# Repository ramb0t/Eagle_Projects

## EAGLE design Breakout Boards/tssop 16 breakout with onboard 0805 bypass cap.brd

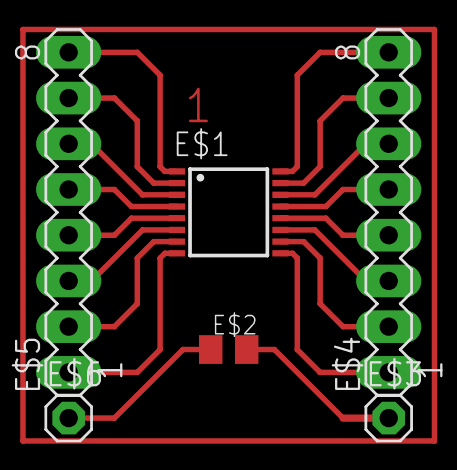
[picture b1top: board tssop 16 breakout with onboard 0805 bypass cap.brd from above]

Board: 2 copper layers, 6 parts (0 on the bottom side), 18 nets.

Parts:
E$1: TSSOP16
E$2: C0805K
E$3, E$6: 1X01
E$4, E$5: MA08-1

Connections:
S$1: E$1.1, E$5.8
S$2: E$1.2, E$5.7
S$3: E$1.3, E$5.6
S$4: E$1.4, E$5.5
S$5: E$1.5, E$5.4
S$6: E$1.6, E$5.3
S$7: E$1.7, E$5.2
S$8: E$1.8, E$5.1
S$9: E$1.9, E$4.1
S$10: E$1.10, E$4.2
S$11: E$1.11, E$4.3
S$12: E$1.12, E$4.4
S$13: E$1.13, E$4.5
S$14: E$1.14, E$4.6
S$15: E$1.15, E$4.7
S$16: E$1.16, E$4.8
S$17: E$2.1, E$6.1
S$18: E$2.2, E$3.1

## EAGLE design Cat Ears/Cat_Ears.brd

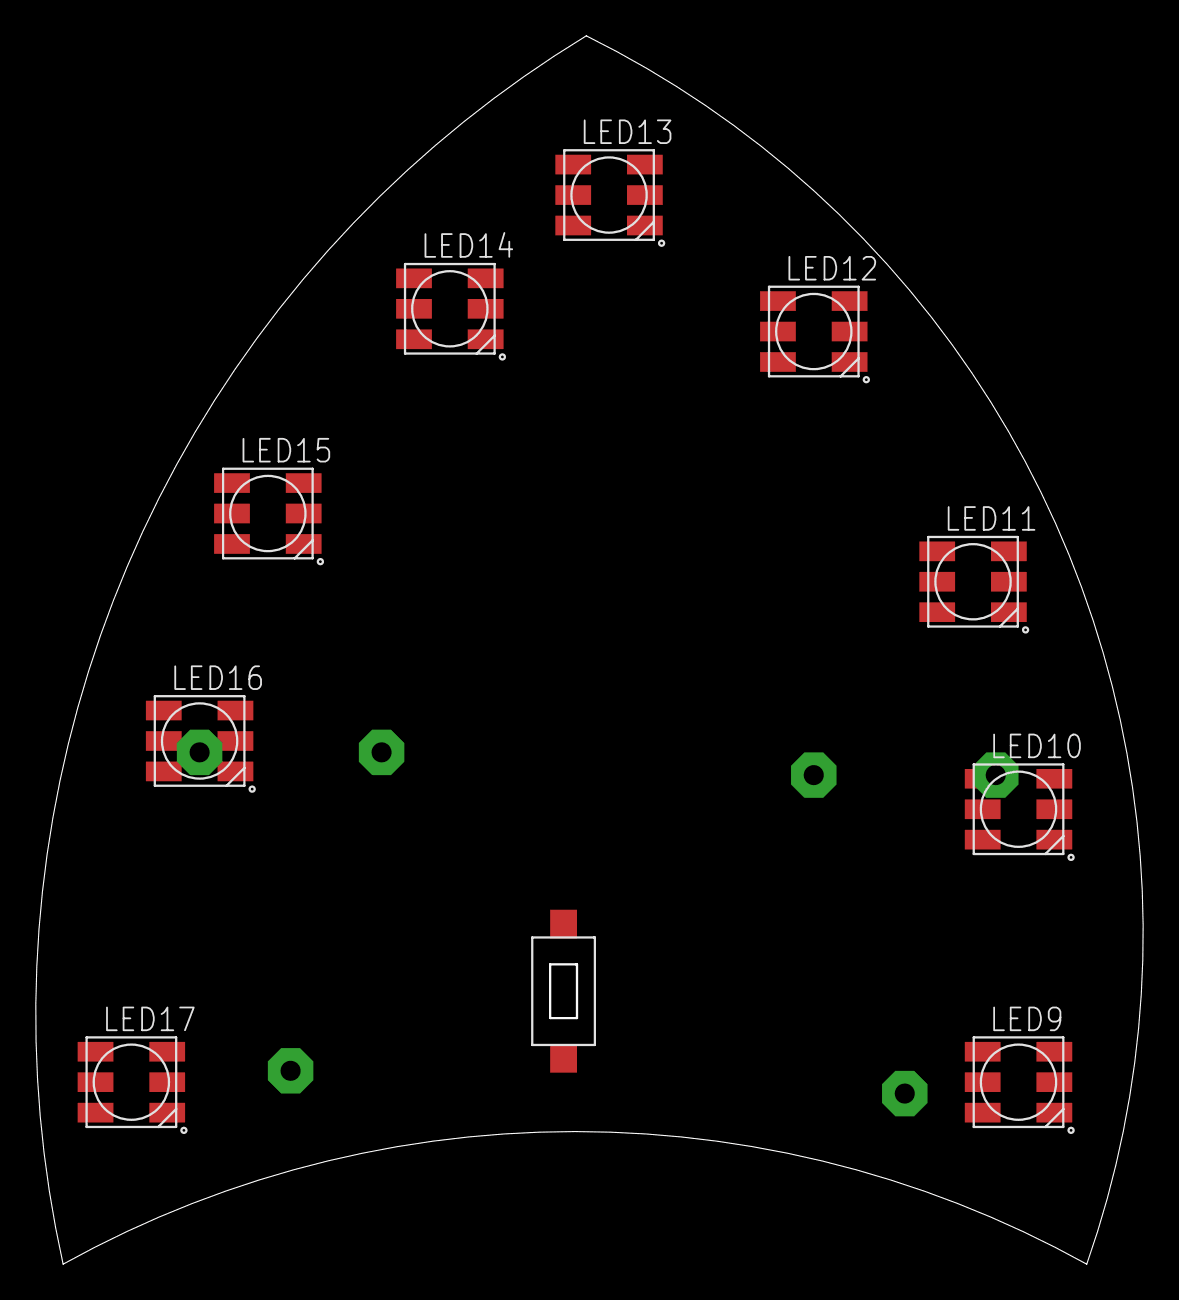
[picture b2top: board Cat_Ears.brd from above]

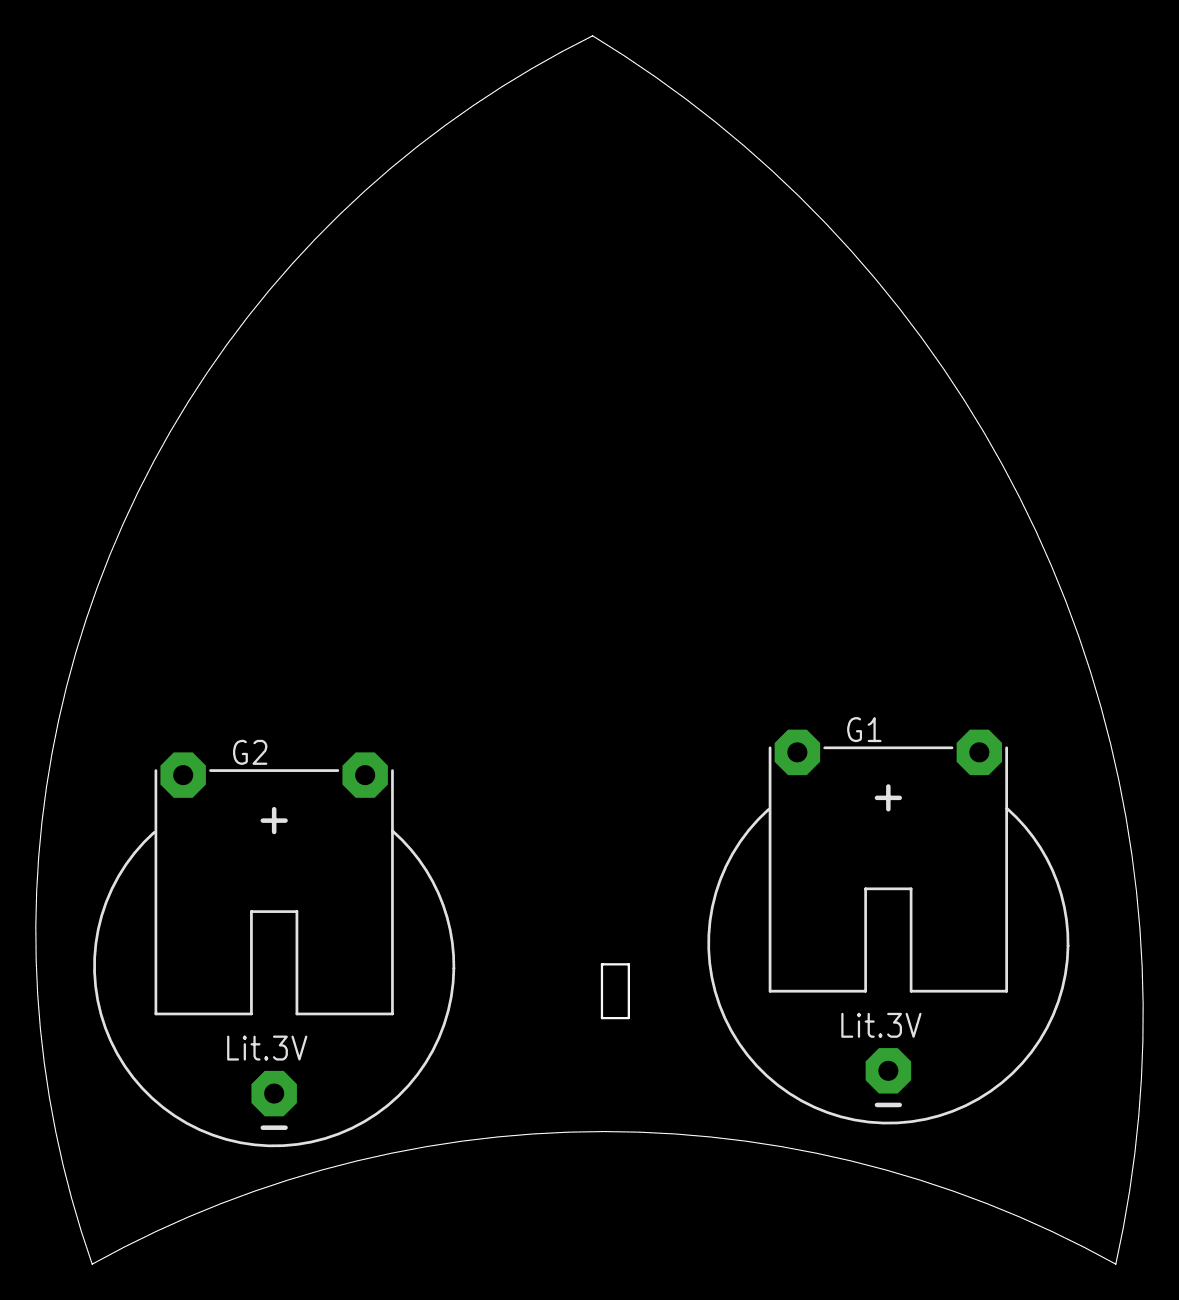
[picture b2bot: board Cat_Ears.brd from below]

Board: 2 copper layers, 61.8 x 68.6 mm, 12 parts (2 on the bottom side), 3 nets, no tracks yet.

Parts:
G1, G2: CR2032H
LED9, LED10, LED11, LED12, LED13, LED14, LED15, LED16, LED17: WS2812
U$1: TS-03M-LF-T

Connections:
GND: LED9.VSS, LED10.VSS, LED11.VSS, LED12.VSS, LED13.VSS, LED14.VSS, LED15.VSS, LED16.VSS, LED17.VSS
LEDVDD: LED9.LEDVDD, LED10.LEDVDD, LED11.LEDVDD, LED12.LEDVDD, LED13.LEDVDD, LED14.LEDVDD, LED15.LEDVDD, LED16.LEDVDD, LED17.LEDVDD
VDD: LED9.VDD, LED10.VDD, LED11.VDD, LED12.VDD, LED13.VDD, LED14.VDD, LED15.VDD, LED16.VDD, LED17.VDD

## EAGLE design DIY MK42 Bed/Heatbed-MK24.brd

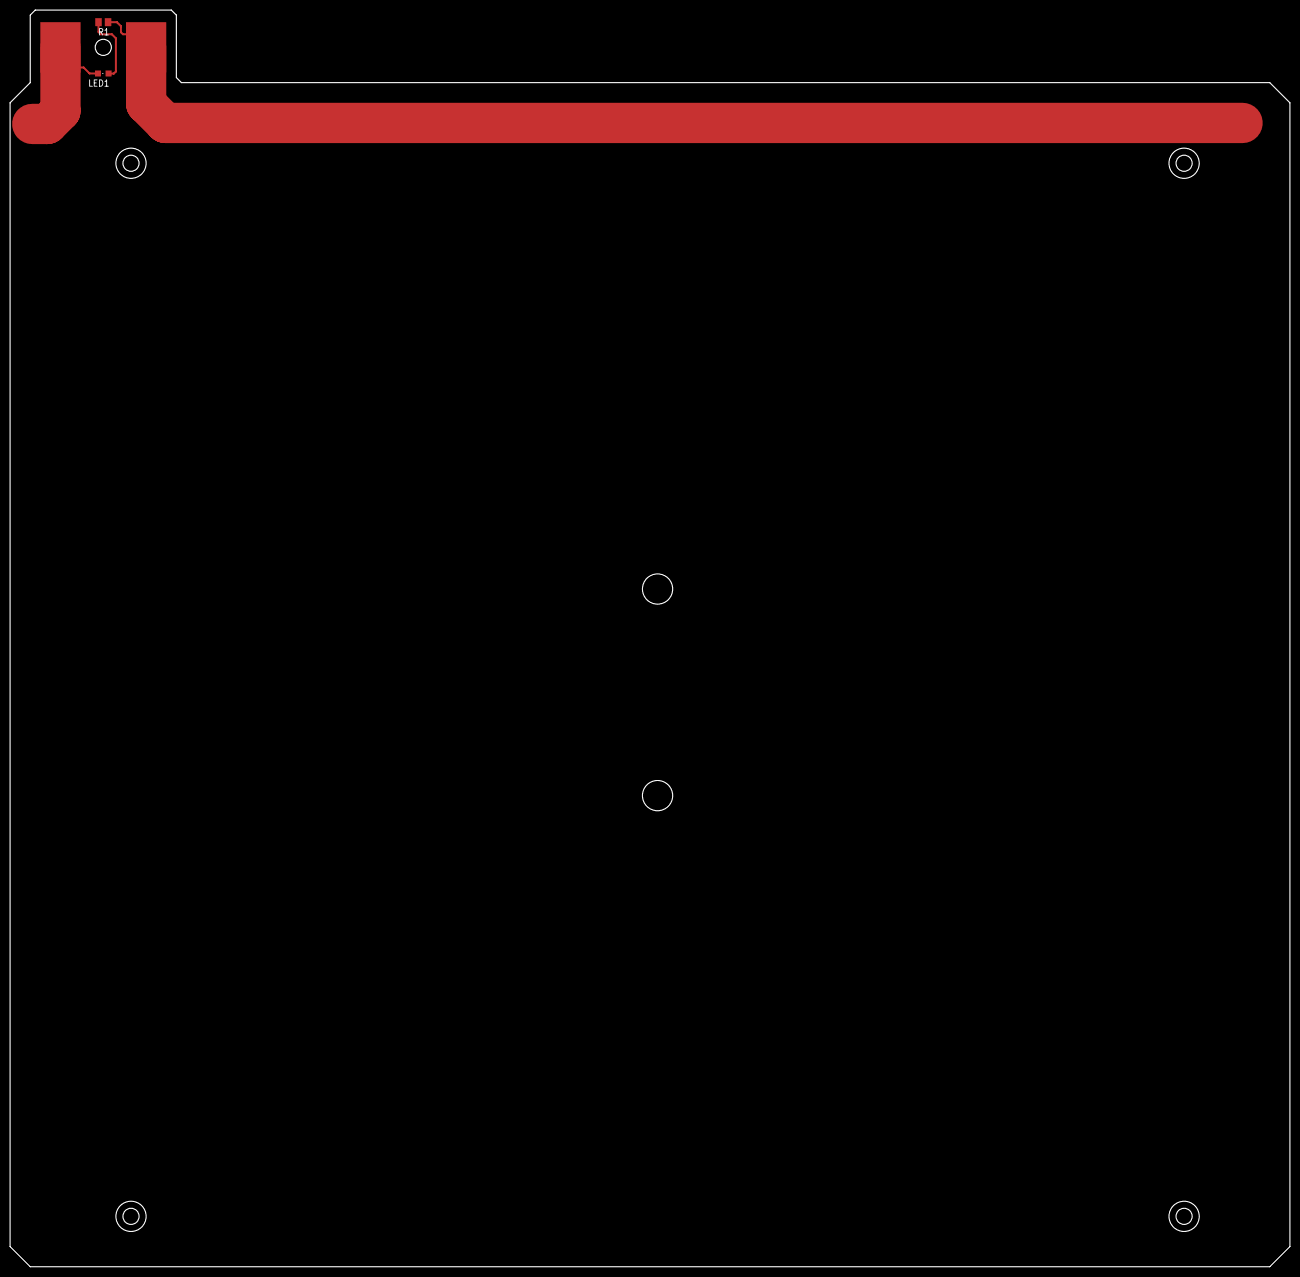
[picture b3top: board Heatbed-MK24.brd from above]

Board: 6 copper layers, 254.0 x 249.4 mm, 4 parts (0 on the bottom side), 2 nets.

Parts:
LED1: CHIPLED_0805
R1: 1k; M0805
U$1, U$2: FASTONSMD

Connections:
HEATER: LED1.C, R1.1, U$1.P$1, U$2.P$1
unnamed: LED1.A, R1.2

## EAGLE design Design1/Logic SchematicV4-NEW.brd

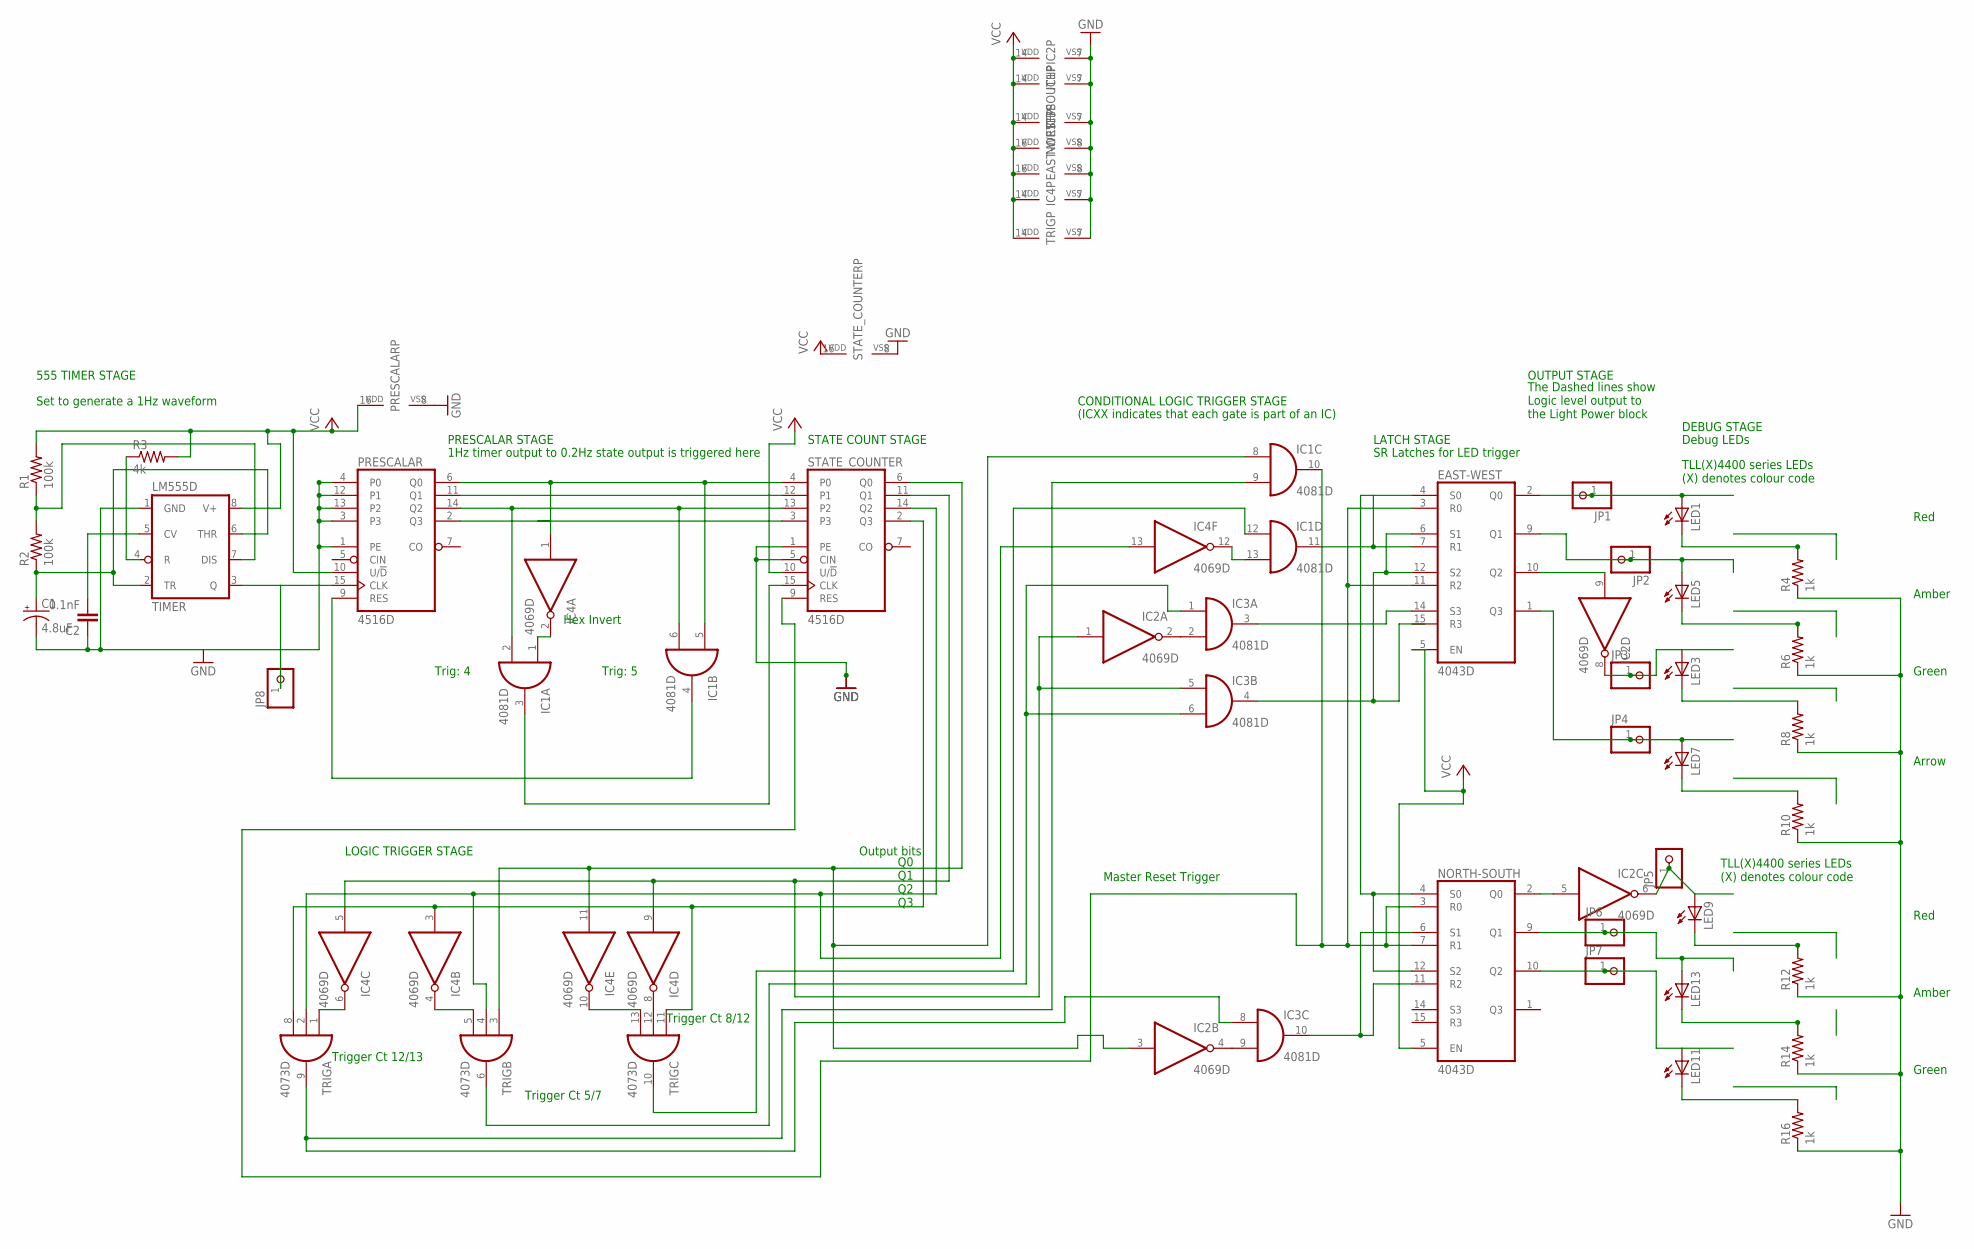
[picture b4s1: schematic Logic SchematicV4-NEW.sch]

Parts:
C1: 4.8uF; E5-8,5
C2: 0.1nF; C0805
EAST-WEST: 4043D; SO16
IC1, IC3: 4081D; SO14
IC2, IC4: 4069D; SO14
JP1, JP2, JP3, JP4, JP5, JP6, JP7, JP8: PINHD-1X1; 1X01
LED1, LED3, LED5, LED7, LED9, LED11, LED13: LEDCHIP-LED0805; CHIP-LED0805
NORTH-SOUTH: 4043D; SO16
PRESCALAR: 4516D; SO16
R1, R2: 100k; M0805
R3: 4k; M0805
R4, R6, R8, R10, R12, R14, R16: 1k; M0805
STATE_COUNTER: 4516D; SO16
TIMER: LM555D; SO08
TRIG: 4073D; SO14

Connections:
GND: C1.-, C2.1, EAST-WEST.8 (VSS), IC1.7 (VSS), IC2.7 (VSS), IC3.7 (VSS), IC4.7 (VSS), NORTH-SOUTH.8 (VSS), PRESCALAR.1 (PE), PRESCALAR.3, PRESCALAR.4 (P0), PRESCALAR.8 (VSS), PRESCALAR.12 (P1), PRESCALAR.13 (P2), R4.1, R6.1, R8.1, R10.1, R12.1, R14.1, R16.1, STATE_COUNTER.1 (PE), STATE_COUNTER.5 (CIN), STATE_COUNTER.8 (VSS), TIMER.1 (GND), TRIG.7 (VSS)
unnamed: PRESCALAR.2 (Q3), STATE_COUNTER.3
unnamed: EAST-WEST.2 (Q0), JP1.1, LED1.A
unnamed: IC1.3 (O), STATE_COUNTER.15 (CLK)
unnamed: C1.+, R2.1, TIMER.2 (TR), TIMER.6 (THR)
unnamed: R1.1, R2.2, TIMER.7 (DIS)
unnamed: C2.2, TIMER.5 (CV)
unnamed: IC1.4 (O), PRESCALAR.9 (RES)
unnamed: IC1.2 (I1), IC1.6 (I1), PRESCALAR.14 (Q2), STATE_COUNTER.13 (P2)
unnamed: R3.1, TIMER.4 (R)
unnamed: PRESCALAR.11 (Q1), STATE_COUNTER.12 (P1)
unnamed: IC2.2 (O), IC3.2 (I1)
unnamed: IC3.10 (O), NORTH-SOUTH.6 (S1), NORTH-SOUTH.11 (R2)
unnamed: IC1.1 (I0), IC4.2 (O)
unnamed: IC4.4 (O), TRIG.5 (I2)
unnamed: IC1.9 (I1), IC3.8 (I0), TRIG.9 (O)
unnamed: IC2.1 (I), IC3.5 (I0), IC4.5 (I), IC4.9 (I), STATE_COUNTER.11 (Q1)
unnamed: IC4.6 (O), TRIG.1 (I0)
unnamed: IC4.3 (I), STATE_COUNTER.2 (Q3), TRIG.8 (I2), TRIG.11 (I0)
unnamed: JP8.1, PRESCALAR.15 (CLK), TIMER.3 (Q)
unnamed: EAST-WEST.9 (Q1), JP2.1, LED5.A
unnamed: EAST-WEST.10 (Q2), IC2.9 (I)
unnamed: IC2.8 (O), JP3.1, LED3.A
unnamed: LED1.C, R4.2
unnamed: LED5.C, R6.2
unnamed: EAST-WEST.1 (Q3), JP4.1, LED7.A
unnamed: IC4.10 (O), TRIG.13 (I2)
unnamed: LED3.C, R8.2
unnamed: LED7.C, R10.2
unnamed: IC3.1 (I0), IC3.6 (I1), TRIG.6 (O)
unnamed: IC4.8 (O), TRIG.12 (I1)
unnamed: IC2.6 (O), JP5.1, LED9.A
unnamed: JP6.1, LED13.A, NORTH-SOUTH.9 (Q1)
unnamed: IC1.13 (I1), IC4.12 (O)
unnamed: JP7.1, LED11.A, NORTH-SOUTH.10 (Q2)
unnamed: LED9.C, R12.2
unnamed: LED13.C, R14.2
unnamed: IC1.12 (I0), TRIG.10 (O)
unnamed: LED11.C, R16.2
unnamed: IC2.5 (I), NORTH-SOUTH.2 (Q0)
unnamed: EAST-WEST.4 (S0), EAST-WEST.7 (R1), IC1.11 (O), NORTH-SOUTH.4 (S0), NORTH-SOUTH.12 (S2)
unnamed: EAST-WEST.14 (S3), IC3.3 (O)
unnamed: IC2.4 (O), IC3.9 (I1)
unnamed: EAST-WEST.6 (S1), EAST-WEST.12 (S2), IC3.4 (O)
unnamed: EAST-WEST.3 (R0), EAST-WEST.11 (R2), IC1.10 (O), NORTH-SOUTH.3 (R0), NORTH-SOUTH.7 (R1), STATE_COUNTER.9 (RES)
unnamed: IC4.13 (I), STATE_COUNTER.14 (Q2), TRIG.2 (I1), TRIG.4 (I1)
unnamed: IC1.8 (I0), IC2.3 (I), IC4.11 (I), STATE_COUNTER.6 (Q0), TRIG.3 (I0)
NOT: IC1.5 (I0), IC4.1 (I), PRESCALAR.6 (Q0), STATE_COUNTER.4 (P0)
VCC: EAST-WEST.5 (EN), EAST-WEST.16 (VDD), IC1.14 (VDD), IC2.14 (VDD), IC3.14 (VDD), IC4.14 (VDD), NORTH-SOUTH.5 (EN), NORTH-SOUTH.16 (VDD), PRESCALAR.10 (U/!D), PRESCALAR.16 (VDD), R1.2, R3.2, STATE_COUNTER.10 (U/!D), STATE_COUNTER.16 (VDD), TIMER.8 (V+), TRIG.14 (VDD)

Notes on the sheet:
Hex Invert
Trig: 4
Trig: 5
1Hz timer output to 0.2Hz state output is triggered here
Set to generate a 1Hz waveform
SR Latches for LED trigger
Debug LEDs
TLL(X)4400 series LEDs (X) denotes colour code
Red
Amber
Green
Arrow
The Dashed lines show Logic level output to the Light Power block
Q0 Q1 Q2 Q3
Output bits
(ICXX indicates that each gate is part of an IC)
555 TIMER STAGE
PRESCALAR STAGE
STATE COUNT STAGE
LOGIC TRIGGER STAGE
Trigger Ct 5/7
Trigger Ct 12/13
Trigger Ct 8/12
Master Reset Trigger
CONDITIONAL LOGIC TRIGGER STAGE
LATCH STAGE
OUTPUT STAGE
DEBUG STAGE

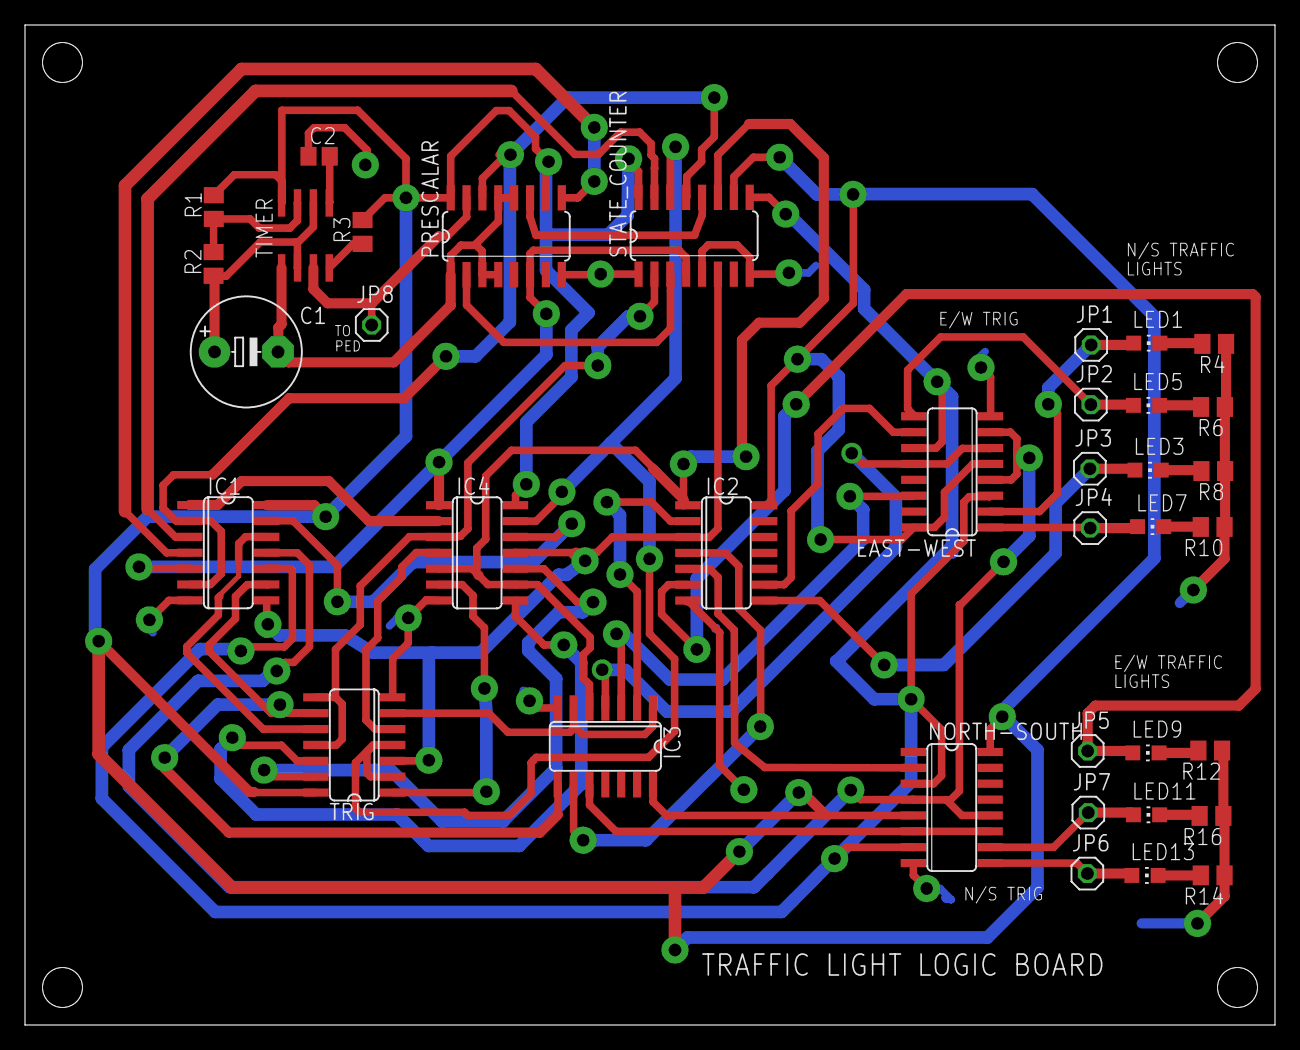
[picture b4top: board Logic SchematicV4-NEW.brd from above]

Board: 2 copper layers, 100.0 x 80.0 mm, 37 parts (0 on the bottom side), 49 nets.

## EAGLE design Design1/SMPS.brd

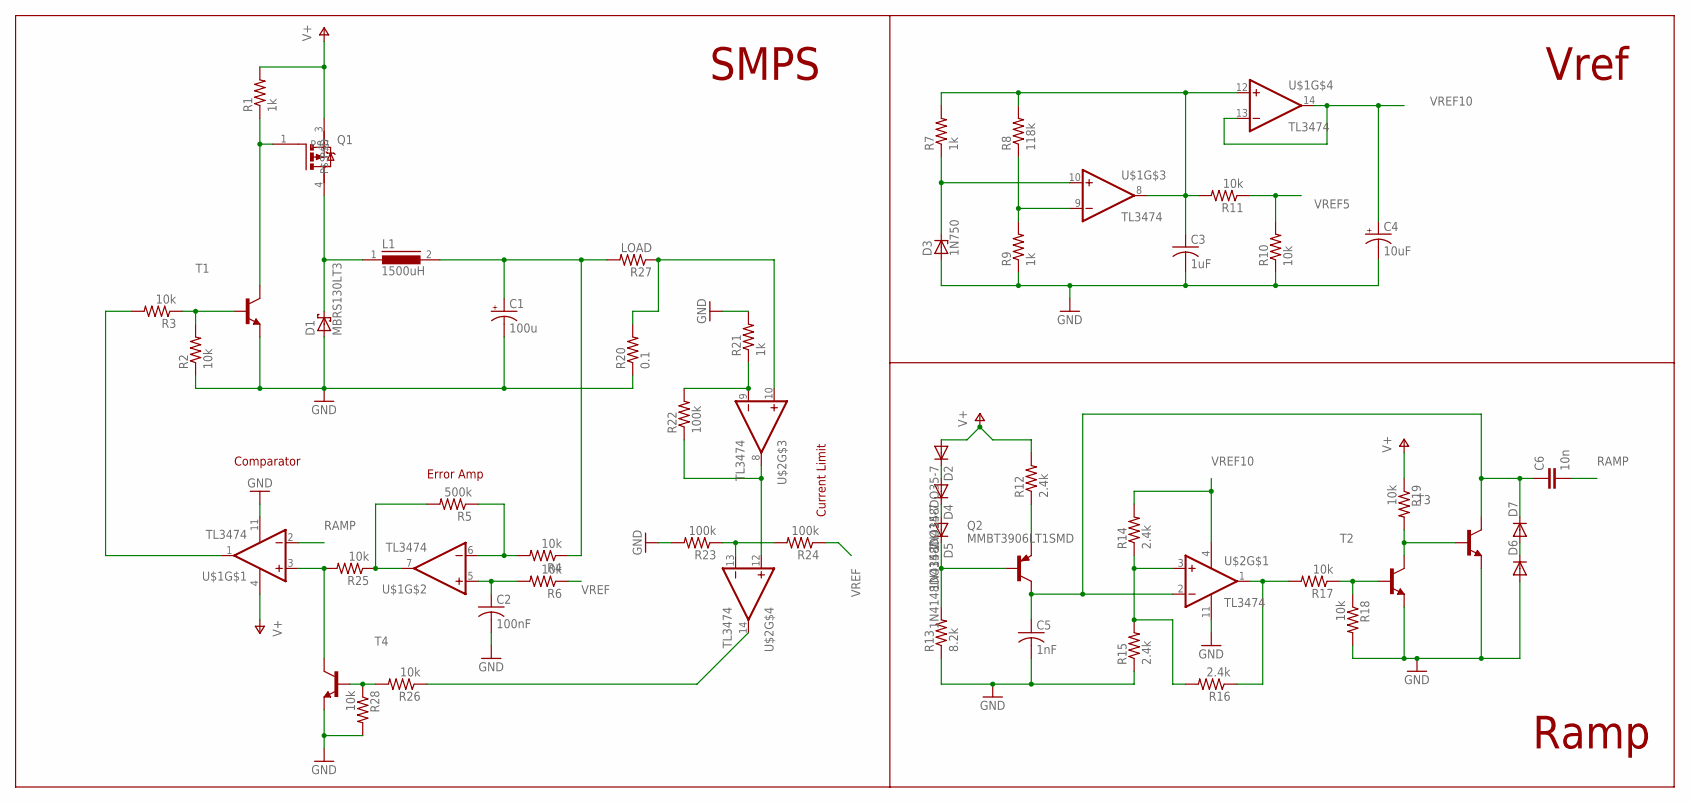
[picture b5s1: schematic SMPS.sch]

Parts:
C1: 100u; E7,5-16
C2: 100nF; C0805
C3: 1uF; C0805
C4: 10uF; E7,5-16
C5: 1nF; C0805
C6: 10n; C0805
D1: MBRS130LT3; SMB
D2, D4, D5, D6, D7: 1N4148DO35-7; DO35-7
D3: 1N750; ZDIO-7.5
L1: 1500uH; 82114R
Q1: IRFR9024NDPAK; D-PAK_TO252AA
Q2: MMBT3906LT1SMD; SOT23-BEC
R1, R7, R9, R21: 1k; R0805
R2, R3, R4, R6, R10, R11, R17, R18, R19, R25, R26, R28: 10k; R0805
R5: 500k; R0805
R8: 118k; R0805
R12, R14, R15, R16: 2.4k; R0805
R13: 8.2k; R0805
R20: 0.1; R1206
R22, R23, R24: 100k; R0805
R27: LOAD; R0805
T1, T2, T3, T4: MMBT2222ALT1-NPN-SOT23-BEC; SOT23-BEC
U$1, U$2: TL3474; SO14

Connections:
GND: C1.-, C2.2, C3.2, C4.-, C5.2, D1.A, D3.A, D6.A, R2.1, R9.1, R10.1, R13.1, R15.1, R18.2, R20.1, R21.2, R23.2, R28.2, T1.E, T2.E, T3.E, T4.E, U$1.11 (V-), U$2.11 (V-)
unnamed: Q1.1 (P$G), R1.1, T1.C
unnamed: R2.2, R3.1, T1.B
unnamed: R3.2, U$1.1 (OUT)
unnamed: C2.1, R6.2, U$1.5 (+IN)
unnamed: D1.C, L1.1, Q1.4 (P$D)
unnamed: C1.+, L1.2, R4.1, R27.2
unnamed: R5.2, R25.1, U$1.7 (OUT)
unnamed: D3.C, R7.1, U$1.10 (+IN)
unnamed: R4.2, R5.1, U$1.6 (-IN)
unnamed: R8.1, R9.2, U$1.9 (-IN)
unnamed: Q2.E, R12.1
unnamed: R20.2, R27.1, U$2.10 (+IN)
unnamed: D6.C, D7.A
unnamed: D5.C, Q2.B, R13.2
unnamed: D4.C, D5.A
unnamed: D2.C, D4.A
unnamed: R14.1, R15.2, R16.2, U$2.3 (+IN)
unnamed: C5.1, C6.1, D7.C, Q2.C, T3.C, U$2.2 (-IN)
unnamed: R21.1, R22.2, U$2.9 (-IN)
unnamed: R16.1, R17.2, U$2.1 (OUT)
unnamed: R17.1, R18.1, T2.B
unnamed: R22.1, U$2.8 (OUT), U$2.12 (+IN)
unnamed: R23.1, R24.2, U$2.13 (-IN)
unnamed: R19.2, T2.C, T3.B
unnamed: R25.2, T4.C, U$1.3 (+IN)
unnamed: R26.2, R28.1, T4.B
unnamed: R26.1, U$2.14 (OUT)
RAMP: C6.2, U$1.2 (-IN)
V+: D2.A, Q1.3 (P$S), R1.2, R12.2, R19.1, U$1.4 (V+)
VR10: C3.1, R7.2, R8.2, R11.2, U$1.8 (OUT), U$1.12 (+IN)
VREF: R6.1, R24.1
VREF5: R10.2, R11.1
VREF10: C4.+, R14.2, U$1.13 (-IN), U$1.14 (OUT), U$2.4 (V+)

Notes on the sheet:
SMPS
Vref
Ramp
Error Amp
Comparator
Current Limit

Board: 2 copper layers, 50 parts (0 on the bottom side), 34 nets, no tracks yet.

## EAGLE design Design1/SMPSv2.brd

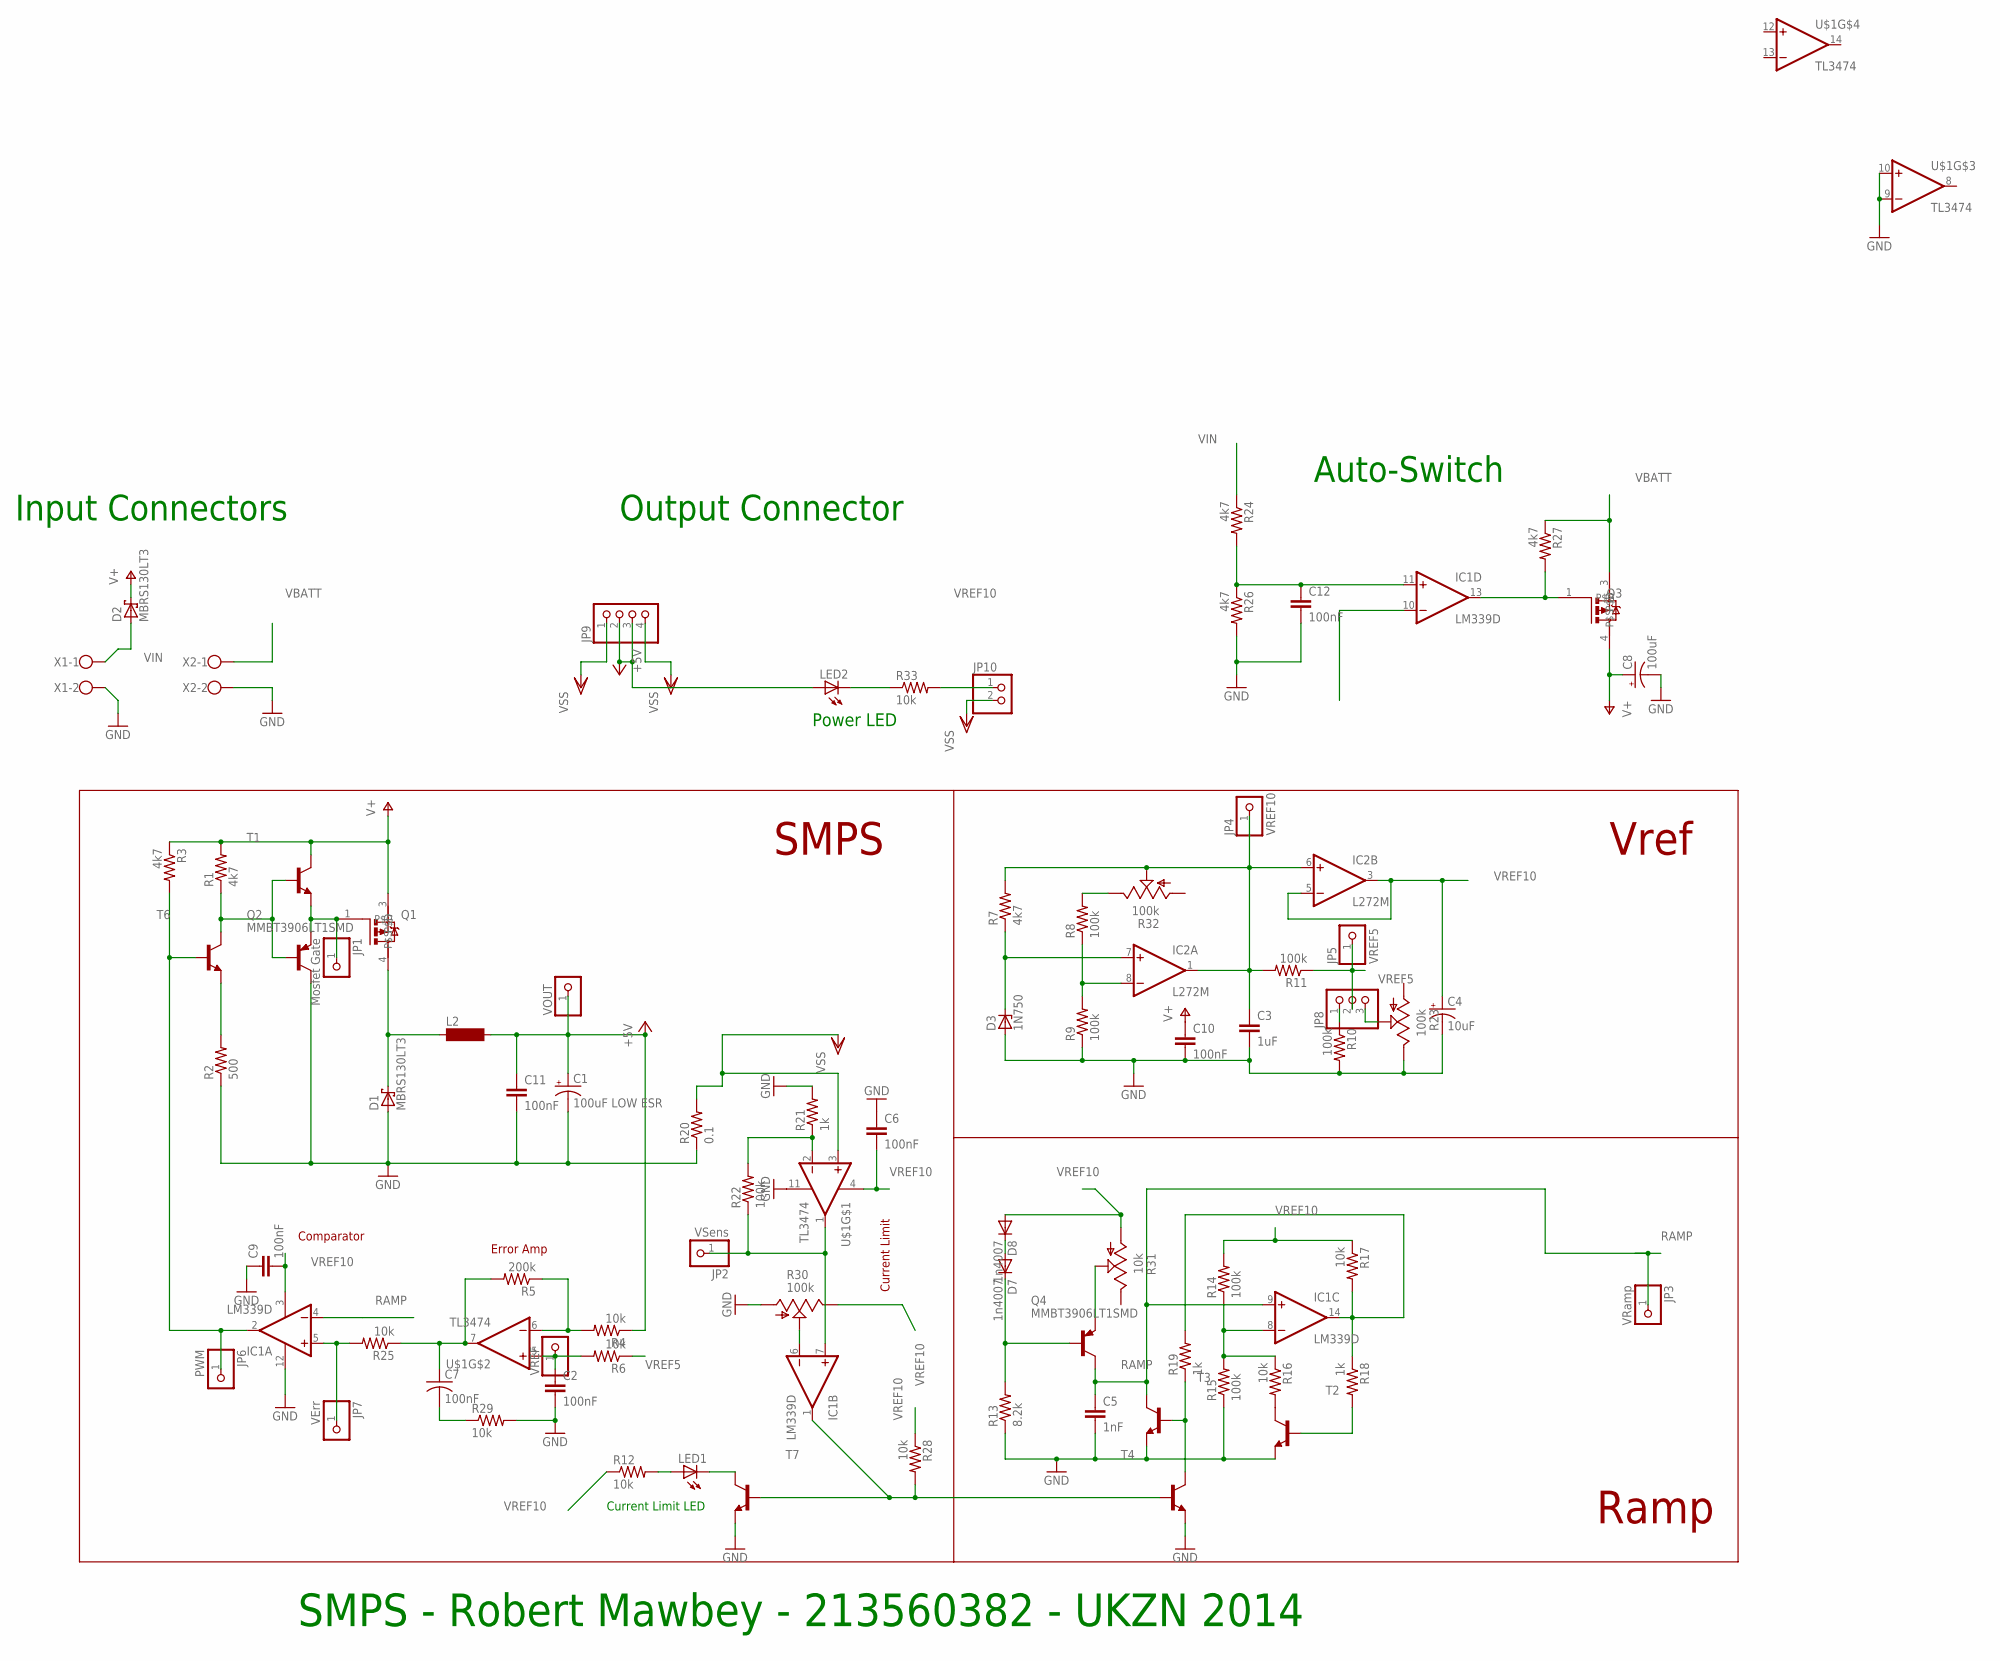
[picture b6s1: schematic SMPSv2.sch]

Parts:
C1: 100uF LOW ESR; PANASONIC_D
C2, C6, C7, C9, C10, C11, C12: 100nF; C0805
C3: 1uF; C0805
C4: 10uF; E5-10,5
C5: 1nF; C0805
C8: 100uF; E5-13
D1, D2: MBRS130LT3; SMB
D3: 1N750; ZDIO-7.5
D7, D8: 1n4007; DO-214AC
IC1: LM339D; SO14
IC2: L272M; DIL08
JP1: Mosfet Gate; 1X01
JP2: VSens; 1X01
JP3: VRamp; 1X01
JP4: VREF10; 1X01
JP5: VREF5; 1X01
JP6: PWM; 1X01
JP7: VErr; 1X01
JP8: PINHD-1X3; 1X03
JP9: PINHD-1X4; 1X04
JP10: PINHD-1X2; 1X02
L2: BS11
LED1, LED2: LEDCHIPLED_0805; CHIPLED_0805
Q1, Q3: IRFR9024NDPAK; D-PAK_TO252AA
Q2, Q4: MMBT3906LT1SMD; SOT23-BEC
R1, R3, R7, R24, R26, R27: 4k7; R0805
R2: 500; R0805
R4, R6, R12, R16, R17, R25, R28, R29, R33: 10k; R0805
R5: 200k; R0805
R8, R9, R10, R11, R14, R15, R22: 100k; R0805
R13: 8.2k; R0805
R18, R19, R21: 1k; R0805
R20: 0.1; R1206
R23, R30, R32: 100k; B25P
R31: 10k; B25P
T1, T2, T3, T4, T6, T7: MMBT2222ALT1-NPN-SOT23-BEC; SOT23-BEC
U$1: TL3474; SO14
VOUT: PINHD-1X1; 1X01
VREF: PINHD-1X1; 1X01
X1: W237-102
X2: W237-102; MPN 237-102

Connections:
+5V: C1.+, C11.1, JP9.2, JP9.3, L2.2, LED2.A, R4.1, VOUT.1
GND: C1.-, C2.2, C3.2, C4.-, C5.2, C6.1, C8.-, C9.1, C10.2, C11.2, C12.2, D1.A, D3.A, IC1.12 (GND), IC2.4 (GND), Q2.C, R2.1, R9.1, R10.2, R13.1, R15.1, R20.1, R21.2, R23.E, R26.2, R29.2, R30.A, T2.E, T3.E, T4.E, T7.E, U$1.9 (-IN), U$1.10 (+IN), U$1.11 (V-), X1.2, X2.2
MSOUT: D1.C, L2.1, Q1.4 (P$D)
unnamed: JP1.1, Q1.1 (P$G), Q2.E, T1.E
unnamed: C7.2, R29.1
unnamed: IC1.2 (OUT), JP6.1, R3.2, T6.B
unnamed: C2.1, R6.2, U$1.5 (+IN), VREF.1
unnamed: Q4.E, R31.S
unnamed: C12.1, IC1.11 (+IN), R24.2, R26.1
unnamed: C7.1, R5.2, R25.1, U$1.7 (OUT)
unnamed: D3.C, IC2.7 (+IN), R7.1
unnamed: R4.2, R5.1, U$1.6 (-IN)
unnamed: IC2.8 (-IN), R8.1, R9.2
unnamed: IC1.13 (OUT), Q3.1 (P$G), R27.2
unnamed: LED1.C, T7.C
unnamed: D7.C, Q4.B, R13.2
unnamed: R19.1, T3.B, T4.C
unnamed: D7.A, D8.C
unnamed: R16.2, T2.C
unnamed: IC1.8 (-IN), R14.1, R15.2, R16.1
unnamed: R21.1, R22.2, U$1.2 (-IN)
unnamed: R18.2, T2.B
unnamed: IC1.6 (-IN), R30.S
unnamed: IC1.7 (+IN), JP2.1, R22.1, U$1.1 (OUT)
unnamed: R8.2, R32.E
unnamed: IC1.1 (OUT), R28.2, T4.B, T7.B
unnamed: IC1.5 (+IN), JP7.1, R25.2
unnamed: LED1.A, R12.2
unnamed: JP8.3, R23.S
unnamed: IC1.14 (OUT), R17.2, R18.1, R19.2
unnamed: Q2.B, R1.1, T1.B, T6.C
unnamed: R2.2, T6.E
unnamed: JP8.1, R10.1
unnamed: LED2.C, R33.1
unnamed: JP10.1, R33.2
RAMP: C5.1, IC1.4 (-IN), IC1.9 (+IN), JP3.1, Q4.C, T3.C
V+: C8.+, C10.1, D2.C, IC2.2 (V+), Q1.3 (P$S), Q3.4 (P$D), R1.2, R3.1, T1.C
VBATT: Q3.3 (P$S), R27.1, X2.1
VIN: D2.A, R24.1, X1.1
VR10: C3.1, IC2.1 (OUT), IC2.6 (+IN), JP4.1, R7.2, R11.2, R32.S
VREF5: JP5.1, JP8.2, R6.1, R11.1
VREF10: C4.+, C6.2, C9.2, D8.A, IC1.3 (V+), IC1.10 (-IN), IC2.3 (OUT), IC2.5 (-IN), R12.1, R14.2, R17.1, R28.1, R30.E, R31.A, U$1.4 (V+)
VSS: JP9.1, JP9.4, JP10.2, R20.2, U$1.3 (+IN)

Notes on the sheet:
SMPS
Vref
Ramp
Error Amp
Comparator
Current Limit
Current Limit LED
Input Connectors
Output Connector
Auto-Switch
Power LED
SMPS - Robert Mawbey - 213560382 - UKZN 2014

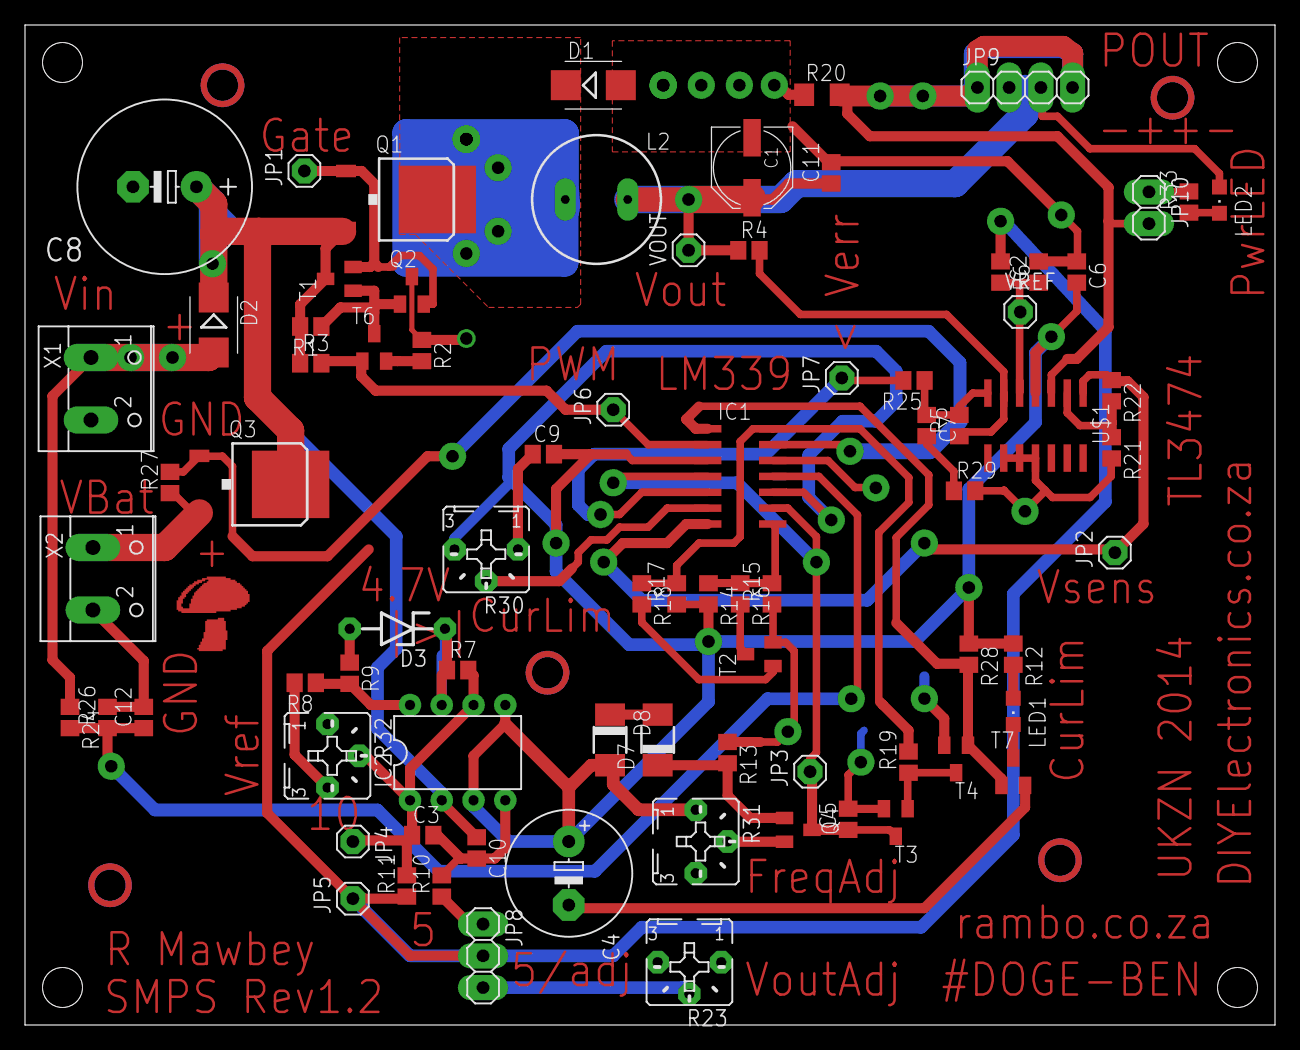
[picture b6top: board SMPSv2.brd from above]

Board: 2 copper layers, 100.0 x 80.0 mm, 80 parts (0 on the bottom side), 43 nets.
